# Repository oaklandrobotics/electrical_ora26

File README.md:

# electrical_ora26
Electrical 2026 for Oakland Robotics

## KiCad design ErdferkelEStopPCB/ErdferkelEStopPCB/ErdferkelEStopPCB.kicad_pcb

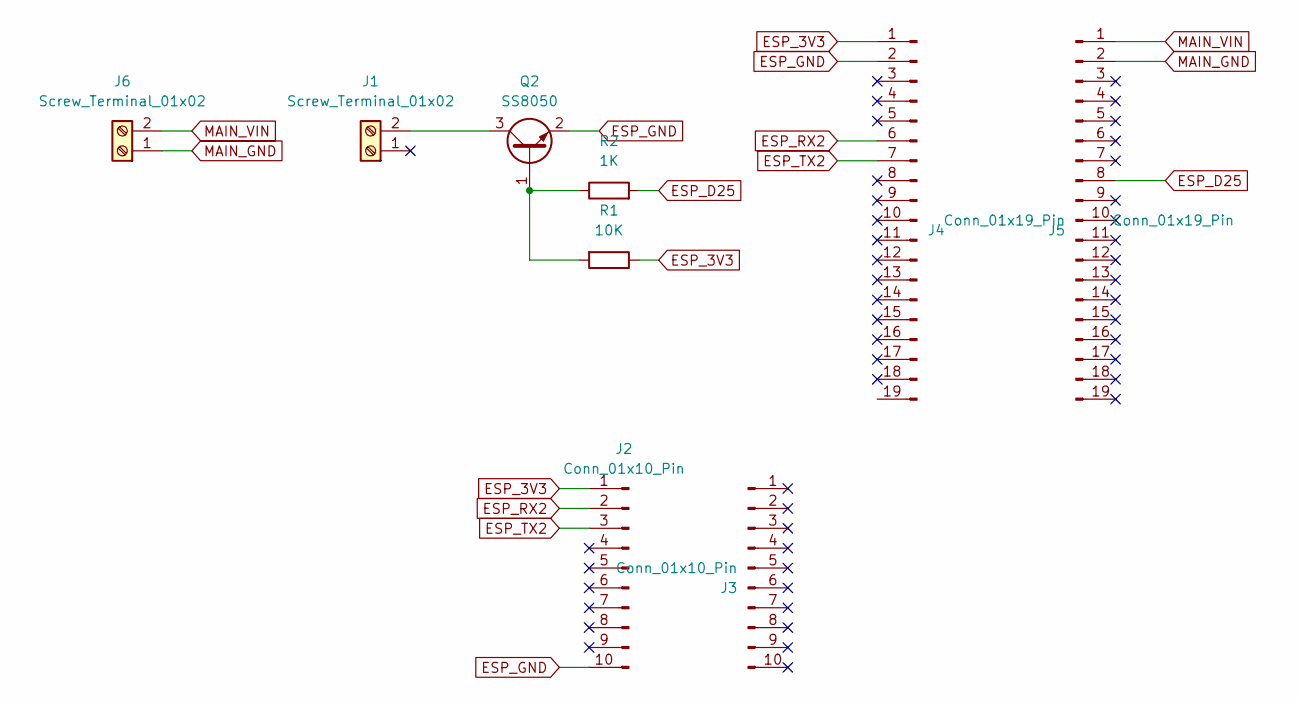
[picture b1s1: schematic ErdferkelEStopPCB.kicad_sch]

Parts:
J1, J6: Screw_Terminal_01x02; TerminalBlock_Phoenix_MPT-0,5-2-2.54_1x02_P2.54mm_Horizontal
J2, J3: Conn_01x10_Pin; PinSocket_1x10_P2.00mm_Vertical
J4, J5: Conn_01x19_Pin; PinSocket_1x19_P2.54mm_Vertical
Q2: SS8050; SOT-23
R1: 10K; R_0805_2012Metric_Pad1.20x1.40mm_HandSolder
R2: 1K; R_0805_2012Metric_Pad1.20x1.40mm_HandSolder

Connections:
ESP_3V3: J2.1, J4.1, R1.1
ESP_D25: J5.8, R2.2
ESP_GND: J2.10, J4.2, Q2.2 (E)
ESP_RX2: J2.2, J4.6
ESP_TX2: J2.3, J4.7
MAIN_GND: J5.2, J6.1
MAIN_VIN: J5.1, J6.2
unnamed: J1.2 (Pin_2_2), Q2.3 (C)
unnamed: Q2.1 (B), R1.2, R2.1

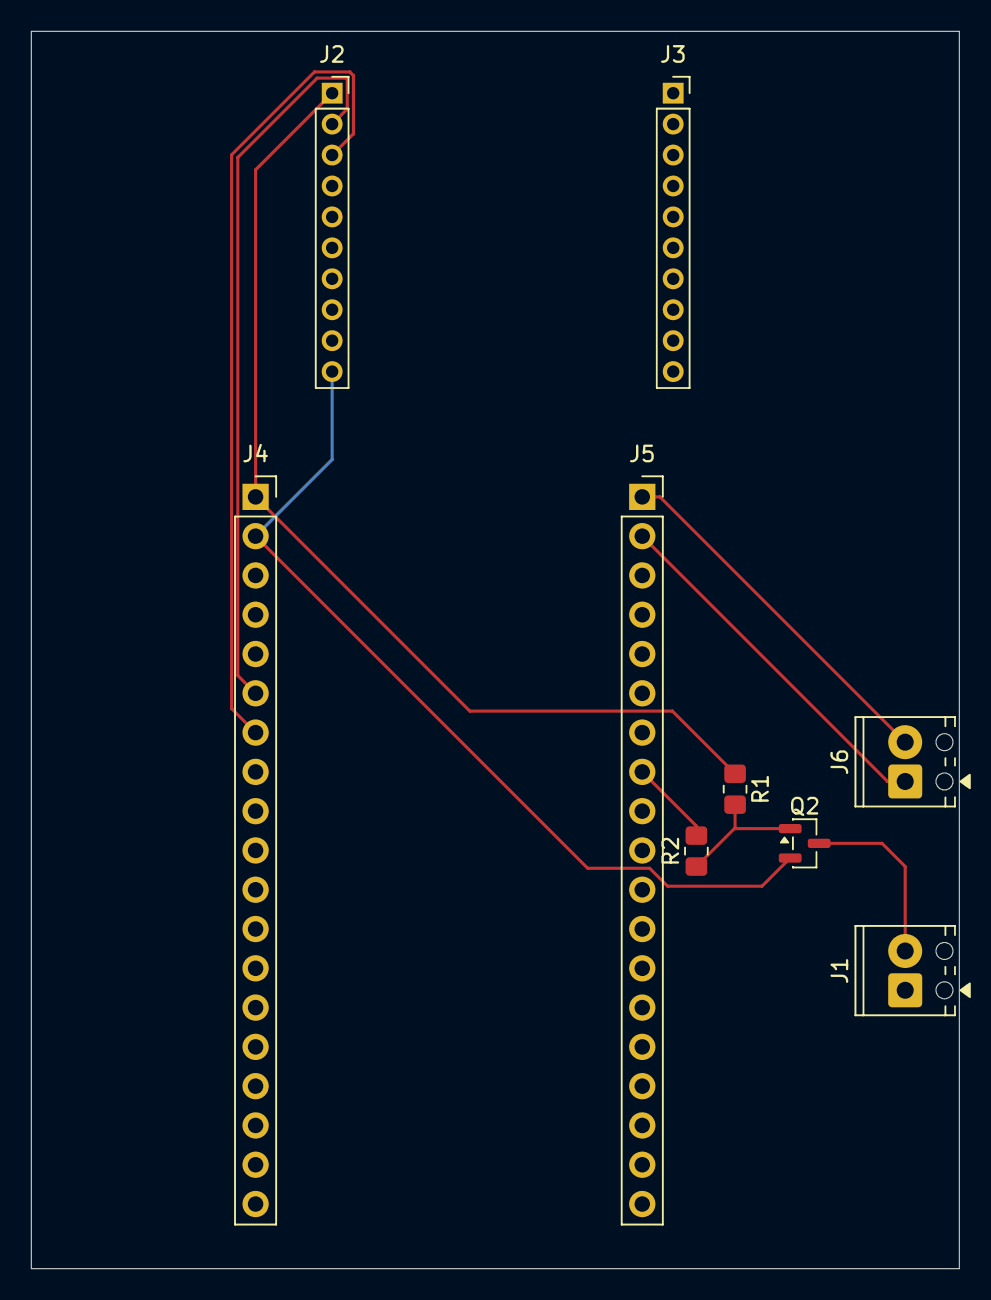
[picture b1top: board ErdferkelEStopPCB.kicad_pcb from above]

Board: 2 copper layers, 60.0 x 80.0 mm, 9 parts (0 on the bottom side), 9 nets.

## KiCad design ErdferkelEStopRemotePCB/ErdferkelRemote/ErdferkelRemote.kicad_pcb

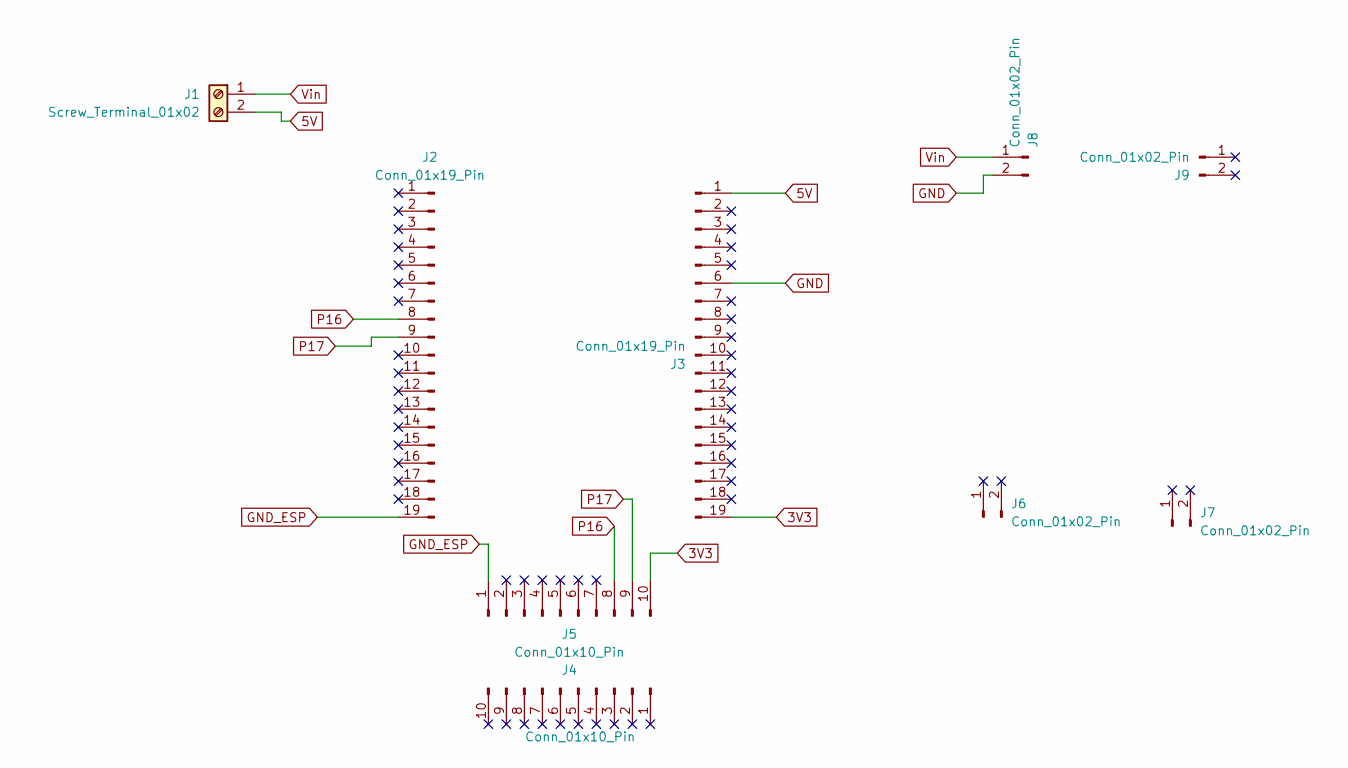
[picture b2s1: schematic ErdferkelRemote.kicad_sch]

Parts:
J1: Screw_Terminal_01x02; TerminalBlock_Phoenix_MPT-0,5-2-2.54_1x02_P2.54mm_Horizontal
J2, J3: Conn_01x19_Pin; PinSocket_1x19_P2.54mm_Vertical
J4, J5: Conn_01x10_Pin; PinHeader_1x10_P2.00mm_Vertical
J6, J7, J8, J9: Conn_01x02_Pin; PinHeader_1x02_P2.54mm_Vertical

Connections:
3V3: J3.19, J5.10
5V: J1.2, J3.1
GND: J3.6, J8.2
GND_ESP: J2.19, J5.1
P16: J2.8, J5.8
P17: J2.9, J5.9
Vin: J1.1, J8.1

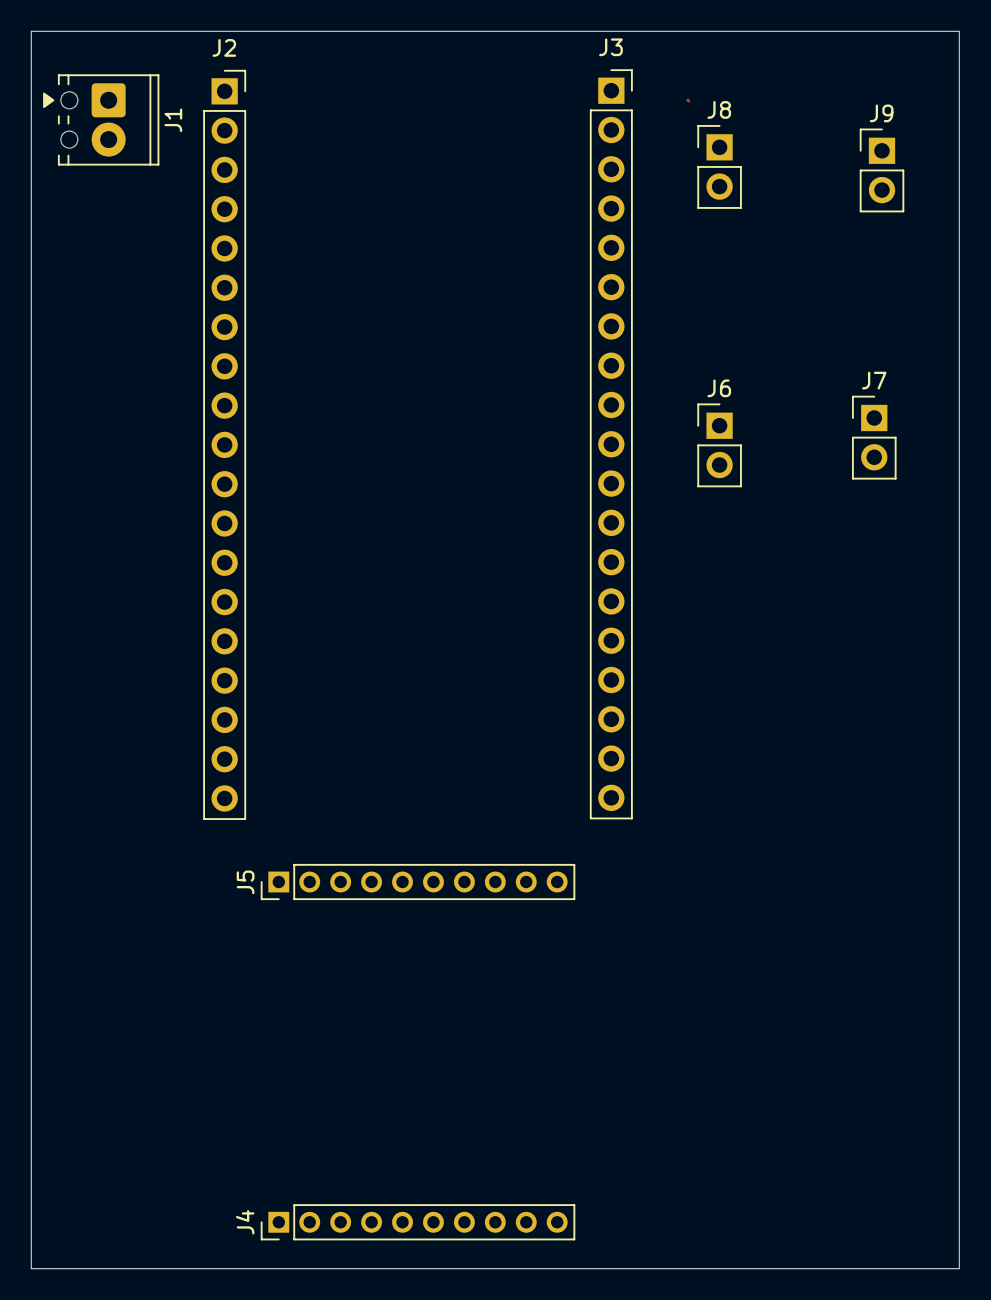
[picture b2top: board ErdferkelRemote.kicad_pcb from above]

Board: 2 copper layers, 60.0 x 80.0 mm, 9 parts (0 on the bottom side), 7 nets.
